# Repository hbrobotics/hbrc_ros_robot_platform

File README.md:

<!--
MIT License

Copyright 2020 Home Brew Robotics Club

Permission is hereby granted, free of charge, to any person obtaining a copy of this
software and associated documentation files (the "Software"), to deal in the Software
without restriction, including without limitation the rights to use, copy, modify,
merge, publish, distribute, sublicense, and/or sell copies of the Software, and to
permit persons to whom the Software is furnished to do so, subject to the following
conditions:

The above copyright notice and this permission notice shall be included in all copies
or substantial portions of the Software.

THE SOFTWARE IS PROVIDED "AS IS", WITHOUT WARRANTY OF ANY KIND, EXPRESS OR IMPLIED,
INCLUDING BUT NOT LIMITED TO THE WARRANTIES OF MERCHANTABILITY, FITNESS FOR A PARTICULAR
PURPOSE AND NONINFRINGEMENT. IN NO EVENT SHALL THE AUTHORS OR COPYRIGHT HOLDERS BE LIABLE
FOR ANY CLAIM, DAMAGES OR OTHER LIABILITY, WHETHER IN AN ACTION OF CONTRACT, TORT OR
OTHERWISE, ARISING FROM, OUT OF OR IN CONNECTION WITH THE SOFTWARE OR THE USE OR OTHER
DEALINGS IN THE SOFTWARE.
-->

# HBRC ROS Robot Platform

The HBRC ROS Robot platform (ie. HR<Sup>2</Sup> or just plain HR2) is a
pedagogical robotic platform for teaching various robotics skills.

This top level document is broken into the following sections below:

* [Google Group](#google-group):
  The Google Group mailing list for this project.

* [Goals/Requirements](#goalsrequirements):
  The goals and requirements for the project.

* [Mechanical](#mechanical):
  The mechanical engineering aspects of the project.

* [Electrical](#electrical):
  The electrical engineering aspects of the project.

* [Software](#software):
  The software engineering aspects of the project.

* [Education](#education):
  The education components of the project.

* [Download, Installation and Workflow](#download-installation-and-workflow):
  The download, installation, and workflow portions of the project.

* [Talks](#talks):
  Various talks given about the project.

## Google Group

There is a Google Groups mailing list to discuss this project at
[HbrcRosRobotPlatform@GoogleGroups.Com](mailto:HbrcRosRobotPlatform@GoogleGroups.Com).
To join the group, visit the
[HBRC ROS Robot Platform web page](https://groups.google.com/d/forum/hbrcrosrobotplatform)
(i.e. `https://groups.google.com/d/forum/hbrcrosrobotplatform`) and request to join.
If that does not work, squirt a quick message to the group manager
(`Wayne` AT_SIGN `Gramlich` PERIOD `Net`) requesting an invitation to join the group.

Not all traffic on the group is going to be interesting to everybody else.
To help out with filtering please put one of the following prefixes at the
front of the each subject line:

* `ALL:` A message of interest to everybody.
* `INST:` A message concerning software installation.
* `ME:` A message to people interested in the HR2 Mechanical Engineering 
  (i.e. solid modeling.)
* `EE:` A message to people interested in the HR2 Electrical Engineering
  (i.e. PCB design, manufacture, bring-up, testing, etc.)
* `SE:` A message to people interested in the HR2 Software Engineering
  (i.e. programs, firmware, etc.)
* `ED:` A message to people interested in the HR2 course materials.
* `DEV:` A message concerning downloading, installation, and development.
* `MSC:` A miscellaneous message that does not really fit any of the above
  protocols.

That should be enough group mailing list structure for starters.

## Goals/Requirements

The list below summarizes the some of the design choices that have been
made so far.

* Start with the Pololu Romi platform used by FPGA class. [Decided]
* Use Patrick's PCB breakout board as a starting point. [Done]
* Consider ditching the Pololu motor board. [Done]
* Work hard to see if the Pololu arm can be bolted on. [Very Likely]
* Try to use USB battery pack instead of AA batteries. [USB Pack yes; AA's no]
* Provide support RasPi 3B+ and RasP4: [yes]
  * 40-pin connector.
  * I2C EEPROM for "hat" identification.
  * Real Time Clock needed for ROS.
  * Various RasPi I2C, SPI, GPO, Serial lines made available.
    *  [Serial: yes, I2C: yes, SPI: probably not, GPIO: OS shutdown
* Some sort of MPU on board:
  * Off the shelf microcontroller board [STM Nucleo-144 Dev. Board format selected]
  * Roomy enough to run MicroPython/MicroROS [STM NUCLEO-F767ZI nominal]
    * ~$25, 216MHz, 2MB Flash, 512K RAM, timers, UARTs, I2C, SPI, Ethernet, etc.
  * Must support C/C++ debugging [ST-Link].
  * Ethernet Phy to talk to boards other than RasPi [Yes]
* FPGA support [custom daughter board required.]
* Arduino support [AVR Dropped. AVR's are expensive/under powered]
* Expansion Capabilities:
  * Arduino Shields. [One can be plugged onto Nucleo.]
  * MikroBus [Iffy, space is tight]
  * Demand Peripherals Connector(s): [On FPGA daughter boards only]
  * Wayne's Bus? [Iffy, space is tight; ouch this hurts!]
  * Grove connectors [Very Likely]
  * Pololu power supply sockets [Iffy, space is tight.]
* Sensors:
  * Motor encoders. [Yes, 1440 step/rev.]
  * Various edge sensors for table top challenge, maze follower, etc.
  * Edge sensors (TOF, IR)
  * Sonars, the are cheap [5 in front, 4 in back.]
  * Servos (arm, camera tilt) [Minimum 4 required]
  * Inexpensive Lidar [Only if the platform is not overloaded]
    * YLidar X2 (~$70)
    * RPLdar A1M8 (~$100)
  * E-Stop [Probably not]
* Camera [RasPi Camera]
* Misc:
  * What issues are missing?

### Mechanical

The mechanical issues are worked out in greater detail in the
[mechancial directory](mechanical/README.md).

The mechanical tasks are:

* Model the Romi platform in OpenSCAD to ensure that the PCB outline
  and mounting holes are correct.
* Model the Romi arm in OpenSCAD to make sure that the Arm does not
  interfere with anything.
* Model both a RasPi 3B+ and RasPi4 for attaching to PCB.
* Model the basic PCB outlines, connector placements, etc.

A short summary of the mechanical design decisions to date are:

* Use the Pololu Romi Platform.
* Use an alternate layout of the motor encoder PCB to free up space to
  support some SBC (Single Board Computers) that are larger than the
  Raspberry Pi footprint.
* Design master board to use an STM Nucleo-144 development board for the
  processor.  All H-bridges, power management, to be put on one board.
* FPGA boards to be done with a a daughter board that plugs into Nucleo-144 board.
 
## Electrical

The electrical issues are worked out in greater detail in the
[electrical directory](electrical/README.md).

Some brief comments on the electrical aspects are:

* The design is to be done using KiCad, since KiCad is 100% free.
* It would be nice to be able to use a simple two layer PCB.
* It would be nice to be able to take power from a USB Power pack.
* It would be nice to support daughter boards for FPGA's.

The overall strategy is to prototype everything using the
[Bantum Labs PCB Milling Machine](https://www.bantamtools.com/)
over at [OLogic](http://www.ologicinc.com/).  This machine is
constrained to only prototyping boards that are 4 inches by 5 inches.
Once the electronics are debugged and working, the PCB's will be
sent out to an appropriate PCB Manufacturing house.

### Software

This section is pretty brief for the moment...

The software issues are worked out in greater detail in the
[software directory](software/README.md).

Terminology:

* Single Board Computer (SBC):
  The nominal SBC for the platform is either the RasPi 3B+
  or the RasPi 4.  Other boards that are compatible with the RasPi
  pin-out *can* be supported, but somebody will have to step up to
  the task of doing the actual support.  The SBC resides on the robot.
* Micro-Processor Unit (MPU):
  This is the micro-controller that is on the main board.
  The nominal processor is ST32Fxxx, where xxx is to be decided.
  The MPU resides on the robot.
* Robot Processors: The robot processors are the SBC and the MPU.
* Development Processor: The development processor is not physically
  attached to the robot.  Instead, it communicates with the robot SBC
  via WiFi.

The software goals are:

* The platform runs ROS on the SBC.
  * Both ROS 1 and ROS 2 are goals with ROS 1 eventually being
    deprecated.
* We need to be able download firmware into the MPU from the SBC.
  This needs to be hands off.
  * Custom C/C++ drivers.
  * MicroPython.
  * Micro ROS.
* The development processor needs to be able to debug code
  running on the robot:
  * Debugging ROS nodes running on the SBC should be relatively easy.
  * Debugging C/C++ code running on the MPU is going to need JTAG
    support.  This can be done with a JTAG chip like the FTDI FT2232.
    This *may* be an "add-on".  OpenOCD can talk to this JTAG chip
    and `gdb` can talk to openocd.
  * Debugging MicroPython is tough.  It currently supports breakpoints
    but does not support data/stack inspection (yet!)
  * As a total stretch, it would be nice to support ARM ETM CoreSight.
    This requires a seriously expensive brick that weighs a ton.
    It is probably a fantasy.
* We need to support FPGA development:
  * We need to be able to download the FPGA chip from the SBC.
  * The FPGA compliation stack needs to run on the SBC and the development
    processor.

## Education

This section is more of a place holder for now...

A partial list of possible educational classes for HR2 platform are:

* Low level robot peripheral drivers.
  * C/C++
  * Micropython
* ROS driver development
  * C/C++
  * Python
* More generic ROS Programming
* Image processing with OpenCV
* AI Frameworks
* Arm manipulation
* PCB design
* MCAD design
  * OpenSCAD
  * Fusion 360
  * FreeCAD
* FPGA class
* Soldering Skills
  * Basic Through Hole
  * Surface Mount
* Rapid PCB prototyping w/Bantum Labs
* etc.

## Download, Installation, and Workflow

Software downloading and installation is done using the following basic steps.

1. [Optional Ubuntu Virtual Machine Installation](#optional-ubuntu-virtual-machine-installation]):
   For now, this project is developed exclusively using a Ubuntu 18.04LTS (Long
   Term Support) Linux distribution.  If you are not running Ubuntu 18.04LTS,
   you need to install it so that it runs using a virtual machine emulation software.
   Otherwise, this step can be skipped.

2. [Download and Install Software](#download-and-install-software):
   The HR2 project uses a diverse set of software.  This software is installed
   using some installation scripts followed by some tried and true technology
   called recursive Make.

3. [Workflow](#workflow):
   Modifications to the documention and design files is done using the
   [GitHub pull request workflow](https://guides.github.com/introduction/flow/).

### Optional Ubuntu Virtual Machine Installation

If you are running on either Windows or MacOS or a non-Ubuntu 18.04LTS Linux distribution,
you need to install Ubuntu 18.04LTS using virtual machine emulation software.  If you are
already running Ubuntu18.04LTS, you can skip this section right now.

There are many
(virtualization)[https://en.wikipedia.org/wiki/Comparison_of_platform_virtualization_software]
software products out there.  If you have a favorite, please feel free to use your favorite
virtualization product.  If you have no favorite, (VirtualBox)[https://www.virtualbox.org/]
is freely available and works.  The remaining instructions are in this section are for
VirtualBox.

Let's start off with some terminology:

* Host Machine:
  The host machine is the actual hardware and associated operating system that VirtualBox
  is running on.

* Guest Machine:
  The guest machine is the virtual hardware and associated operating system that is running
  under the VirtualBox software.  In this case, the guest machine is running Ubuntu18.04LTS.

The basic steps involved are:

1. Download VirtualBox:
   Visit the [VirtualBox Downloads] web page and follow the instructions appropriate
   for your host machine.

2. Download Ubuntu18.04LTS:
   [Download Ubuntu18.04 LTS](https://ubuntu.com/download/desktop) to your host machine.
   This shows up as a file with an `.iso` suffix.
   
3. Configure a VirtualBox Virtual Machine.
   Start VirtualBox software and a Graphical User Interface (GUI) should show up on your
   screen.

   Click on the [New...] button to bring up create pop-up window.

   A. Name and operating system:
      * Name: Pick a name, (suggestion: "Ubuntu18.04LTS").
      * Machine Folder: (Use the default.)
      * Type: Pick [Linux]
      * Version: Ubuntu (64-bit)
      * Click on [Next>].

   B. Memory size:
      * At least 4096 MB is recommended.  Do not use 1024 MB.
      * Click on [Next>]

   C. Hard disk:
      * Select "Create virtual hard disk now".
      * Click on [Create]

   D. Hard disk file type:
      * Select "VDI (VirtualBox Disk Image0"
      *Click on [Next>]

   E. Storage on physical hard disk:
      * Select "Dynamically allocated"
      *Click on [Next>]

   F. File Location:
      * Use the default file folder.
      * Increase the file size to at least 20 GB. 30 GB or 40 GB is preferred.
      * Click on [Create] to create the virtual machine and dismiss the pop-up window.

   G. Configure network:
      * Click on the [Settings...] Button to bring up [Settings] pop-up window:
      * Change "Attached to:" from "NAT" to "Bridged Adapter"
      * Click on [OK] to dismiss the pop-up window.

   The virtual machine is configured and ready to run.

4. Install Ubuntu18.04LTS.

   A. Start the virtual machine by either double clicking on the machine name or clicking
      on the [Start] button.  Please note that the guest machine and host machine can
      fight over who has the keyboard and mouse.  There are two control keys on your
      keyboard, one to the left of the space bar and the other to the right of the space bar.
      The right control key is used break up the fighting over mouse/keyboard input destination.
      If you are going "what happened to my mouse cursor are where are my keystrokes going"
      use the right control key to change things.

   B. After starting the virtual machine, VirtualBox will bring up a pop-up window
      asking you to select a virtual CD Rom image to to insert into the virtual optical
      disk drive.  Please use the file choose to select the Ubuntu 18.04LTS `.iso` file
      you previously downloaded.

   C. Click on [Install Ubuntu].

   D. Select your keyboard.

   E. Select: "Normal installation and download updates".

   F. Select: "Erase disk and install Ubuntu".
      * (Since this is virtual machine you can safely ignore the scary warning.)
      * Select Click on [Install Now]
      * Click on [Continue].

   G. Time Zone:
      *Select the correct time zone.

   H. Account setup:
      * Your name:
        Use your properly capitalize first and last name.
      * Your computer's name:
        Using a lower case name pick a name for the computer.
        For exam
      * Pick a user name:
        All lower case and one word.
      * Choose a password...:
        Type in your password twice.
      * Select "Require my password to log in".

   H. The installation takes some time.

   I. Click on [Restart Now]

   J. Ignore the "Please remove the installation medium" message, just press [Enter].

   K. Just type [Enter] for the Grub splash screen.

   L. Click on you user name and type in your password.

   M. Click through the startup screens.

   N. If the software updater window pops up click on [Install Now] and type in your password.
      If it pops up a restart machine window, just ignore it for now.

5. Install Guest Additions

   The guest extensions provide a more seamless integration between VirtualBox and
   the host machine.  For some reason, the documentation at for VirtualBox guest
   extension installation is actually pretty confusing.  Please try the instructions below:

   A. Bring up a terminal window by typing [Ctrl-Alt-T]  (use the left [Ctrl] key.)

   B. Type the following commands.  `sudo` will probably prompt you for your password.
   
      * `sudo apt update`
      * `sudo apt install build-essential dkms linux-headers-$(uname -r) --yes`

   C. Click on [Devices => Insert Guest Additions CD Image...]

   D. It should ask if it is OK to run some files.  Click [OK].

   E. Type in your password and click [Authenticate].
      This can take a while.

   F. Type [Enter] when [Press Return to close this window...] shows up.
      If your virtual machine reboots you can skip the next step.

   G. (Optional) If for some reason the virtual guest extensions do not properly
      install.  The following commands provide and alternative way of
      getting them installed.  Now run the following commands:

      * `sudo mkdir -p /tmp/cdrom`
      * `sudo mount /dev/cdrom /tmp/cdrom`
      * `sudo sh /tmp/cdrom/VBoxLinuxAdditions.run --nox11`
      * `sudo shutdown -r now`

      The machine should reboot.

   H. Select your user name and login with your password.

   I. Resize the virtual machine window to make sure the guest additions have taken hold.
      The background window should fill as it resizes.  If not, it will stay at a fixed
      size and something has gone wrong with your guest additions install.

   J. In the upper right corner there is a downward pointing triangle.
      Click on it and select [power off].
   
   Your virtual machine is installed and in a powered down state.

6. Make a clone.

   Installing all of the software is sufficiently painful that it is desirable
   to avoid having to do it again.  VirtualBox allows you to make a clone of
   an existing system so that the original system can be reused in the future.
   It is really easy and does not consume very much extra disk space,
   so making a clone is strongly recommended.

   A. Bring up the VirtualBox manager window again.

   B. Right mouse click on the name of your virtual machine:

      * Name: Give the clone a new name like "Ubuntu18.04LTS_HR2"
      * Path: Use the default
      * MAC Address Policy: Use the default
      * Leave the additional options unclicked.
      * Click [Next>] to go to the next pop-up window.

   C. Clone type

      * Select [Linked clone].  This saves lot's of disk space
      * Click on [Clone] to finish the clone.

   D. Now start the clone by by double clicking on it.

## Download and Install Software

The software is generally deployed in three broad catagories:

* Ubuntu packages: for basic tools and software (e.g. Kicad, OpenSCAD, etc.)
* Cloned Git Repositories: this project and some projects it depends upon used
  `git` repositories.
* Python `pip` packages: There is lots of Python 3 code sprinkled around this project
  and a bunch of it is packaged up as Python packages that can be installed with
  the Python `pip` program.  (By the way, `pip` stands for `Pip Installs Packages`.)
  There is heavy use of a technology called Python Virtual Environments.

There will be a number of cloned git repositories and they need to reside as
separate sub-directories under one parent repository directory.  (One parent
directory to rule them all!)  You can call this parent directory whatever you
want -- `repos`, `projects`, `funstuff`, `sauron`, etc.  For the directions
below we use `REPOS` for this parent directory name.  Please substitute the
directory name you picked for `REPOS` in the directions below:

### Clone 

There are 3 broad steps:

1. The first step is to clone the `hbrc_ros_robot_platform` repository.
   Let's get going:

        cd .../REPOS   # Change the current working directory to REPOS
        # We need to get `git` installed.
        # If `git` is already installed, skip the install below:
        sudo apt install git --yes # You may be asked for your user password:
        # Now "clone" the `hbrc_ros_robot_platform` repository using `git`:
	git clone https://github.com/hbrobotics/hbrc_ros_robot_platform.git
        # Change the current working directory to the root of the cloned repository
        cd hbrc_ros_robot_platform
	# Set your `git` user name and `email`.  Please run the following two commands:
        git config --global user.name "Your Name"
        git config --global user.email "youremail@yourdomain.com"

2. The second step is to run one `hr2_install` script.  This is done by

     ./bin/hr2_install OPTION

   where `OPTION` is one or more of the following:
   * `all`:  Installs everything.
   * `most`: Installs everything but `dev`.
   * `dev`:  Installs the development workflow (a personal Git.Hub account is required.)
   * `ee`:   Installs all of the software needed for electrical engineering.
   * `me`:   Installs all of the software needed for mechanical engineering.
   * `sw`:   Installs all of the software needed for software development.

   Many people select the `most` option.

   Downloading everything takes quite a while (frequently in excess of half an hour.)
   Sometime you will be prompted for your user password so that the system can install
   some system software.  The `stm32cubeide` software download (selected by `ee`, `me`)
   is particularly slow.
     
3. After the `hr2_install` script terminates (
   This is important.  You need to activate your Python Virtual environment.
   This is done as follows:

     source ~/.bashrc
     workon hr2   # Activate the hr2 Python virtual environment

4. After that yo can use the `make` program to do any remaining buidling.

   Use the `make` program to recursively build `everything` by typing:

           make everything

Installing is a notoriously fragile process and it is quite possible that
something can go wrong.  If so, please send a message to the group list with
the `DEV:` prefix on the subject line explaining the issue so it can be resolved.

### Workflow

Workflow is a generic term for how modifications are made to this project.

Examples of such modifications are.

* Modifying the mechanical models,
* Modifying electrical design and associated printed circuit board designs,
* Modifying the software,
* Fixing documentation errors,
* Developing educational course materials, Etc.

Some terminology here.  We are going to use the pronoun "you" to mean "you the
person doing project development" in the description below.

#### Workflow Introduction

There are two common workflows supported by GitHub.com:

* Shared Repository Workflow:
  This is the simplest model where there is one common shared parent repository stored
  at GitHub.com and you have local cloned copy of the shared parent repository stored
  locally on your development machine.  You develop and test your changes on your local
  machine.  When you decide your changes are "ready", you "push" the changes back up to
  the shared parent repository on GitHub.com.  Over time, you and other developers
  "pull" the accumulated changes stored in the parent repository down into your
  respective local repositories to stay up to date.  This workflow is extremely
  common and has been supported by many version control systems for literally decades.

* Fork and Pull Request Workflow:
  In this model, the common parent repository is the same as the shared repository
  workflow immediately above.  However, now you need two repositories to do development.
  The first repository is the same local repository on your local machine as before.
  In addition to your local repository, you also have your own semi-private
  repository stored on GitHub.com that is used for staging purposes.  This staging repository
  is goes by a less descriptive name called a "fork repository".  Your fork repository
  is "connected" to the shared parent repository.  Since there are multiple developers,
  there multiple "forks" of the same shared parent directory on GitHub.com, where each
  is stored in a different user account to keep them separate from one another.

  The workflow is that you make modifications to your local repository and "push"
  them up to your staging "fork" repository.  Next, you generate something called
  a "pull request".  (Frankly, the term "pull request" is miss-named, it should be
  called a "merge request".  It is too late to change the terminology now, so we
  will stick with the less descriptive term of "pull request".)  The details of how
  to generate a "pull request" are discussed  little be further below.  The "pull request"
  generates an E-mail that is sent to one or more reviewers.   The reviewer looks at your
  changes using the GitHub.com GUI (Graphical User Interface.)  If the reviewer likes
  the changes, they are immediately accepted and merged from your fork repository to
  the shared master repository.  If any reviewer has some issues, an E-mail dialog ensure
  where the reviewer says things like "I really like this!", "This won't work because ...",
  "Fix this tiny issue", "What about doing it this way...", and an occasional
  "No way because..."  As a result of some of the review comments, you may need to make
  additional changes and push them up to the fork repository.  When the pull-request
  E-mail exchange dialog dies down and all of your changes have been pushed up to your
  fork repository, the reviewer accepts the changes and merges them into the
  shared parent repository.  The "Fork and Pull Request Workflow" is shown immediately
  below using some crude ASCII art:

                [Shared Parent]<---------------[Simi-Private Fork]   GitHub.Com
                       |                                ^
                ====== | ============================== | =====================
                       v                                |
                       +--------->[Private Local]------>+         Local Machine
                        
                         Fork and Pull Request Workflow
			   
The key advantage of the Fork and Pull Request work flow is that you do not need
permission from anybody to start making your changes.  You start your changes locally
and ask for permission only after you think they are ready.  When the reviewer
agrees, your changes are merged in.

It should come as no surprise to you that this project is using the fork and pull
request workflow.

#### Workflow Setup

If you have followed the download and install instructions above, you have a
local copy of the `hbrc_ros_robot_platform` repository as a sub directory under
your REPOS directory.  What you do not have is a staging fork repository *AND*
you have not configured `git` to do an asymmetric pull and push.  The instructions
below will remedy these issues.

Most of the tools you need to do the Fork and Pull Request workflow are already mostly
in place.  The primary tools are `git` and a program called `hub` which is a command
line interface to the GitHub.Com functionality.  We will do as much of the set up using
a command line tools as possible because the command line tools tend not to change as
fast as the web interface changes.  (If you are already comfortable the GitHub.Com web
interface, you can probably skip some of the steps below and use the web interface instead.)

There are a still a few manual steps to do:

1. The first step is to create your own personal account on GitHub.Com.  This is done
   visiting the main [GitHub.Com web page](https://github.com/) web page.  You need to
   specify a unique "Username" (all lower case with no spaces or punctuation is recommended),
   an "Email" address, and a "Password".  There will be a message sent your E-mail address
   that you must respond to with a response E-mail to finish the account creation.  The
   "Username" is your GitHub.Com account name and will be needed further below.  Do not
   log out of GitHub.Com yet.

2. In order to avoid having to type in a password all the time, you need to set up your
   computer to use an SSH key to talk to your GitHub.Com account.  The install scripts
   have ensured that an SSH key has been generated.  The public key is stored at
   `~/.ssh/id_rsa.pub`.  There is a
   [GitHub.Com SSH Key Installation](https://help.github.com/en/github/authenticating-to-github/adding-a-new-ssh-key-to-your-github-account) web page that will guide you through the GitHub.Com
   web interface to install your public SSH key.  It is a little tedium for now, but will avoid
   much password prompting annoyance in the future.  If you are lucky, you should not need
   to deal with the GitHub.Com web interface any more.  Now you can disconnect from GitHub.Com.

3. Add GITHUB_ACCOUNT_NAME variable definition to your `~/.bashrc` file.  This is typically
   done a the end of the file by adding a line that looks like:

      GITHUB_ACCOUNT_NAME=whatever_you_typed_in_in_the_previous_step
      source ~/.bashrc  # Do no forget this step.

4. Please rerun the `hr_install dev` to get your development environment set uo.

That pretty much wraps up the additional steps need to enable the "Fork and pull-request"
workflow.  Next, it is time to try it out.

#### Workflow Usage

The `git` program does a great deal of stuff and it is outside the scope of this
document to attempt to cover it all.  Instead, we will explain just enough to get started.

If you have followed the steps above, you have a repository named `hbrc_ros_robot_platform`
sitting on you local machine.  Your local repository has the following characteristicx:

* It has `upstream` remote descriptor that points to the shared project repository.
* It has `staging` remote descriptor that points to the semi-private forked directory
  that is used for staging purposes.
* The `master` branch which has be set up so that it only accepts updates from the
  `upstream` remote.

The first thing to understand is that you should never to development on the `master`
branch.  We have tried to make it difficult for you to screw up `master`, but somebody
who really wants to can screw it up anyhow.

The second thing to understand is that all development takes place in one or more
side branches, called development branches.  The way to create a new branch is by

     git checkout -b NEW_BRANCH_NAME master

where you supply a new and hopefully descriptive name for the new development branch.
After this command, the new branch will be active.  Now you can modify things to your
hearts content.  You can check the files in as many times as you want using `git add ...`
and `git commit -m "SOME MESSAGE HERE."`.  You can perform as many commits as you want
on the branch.  Please put descriptive comments in the commit logs.

When you think you changes are ready to be merged into the project you initiate
a pull-request.  This is done by the command:

     pull_request

This command is in the repository `bin` directory.  This will ensure that you have
merged with the `master` branch, push your commit up to the staging repository and
generate a pull request.  You will have add a comment into the pull request via an
editor that will pop up.

Just so you know, there is a command called `master_merge` that will ensure that
the `master` branch is up to date with GitHub.Com and then attempt to `master` branch
to be merged with your current branch.  This command is invoked by `pull_request`, but
you can invoke it yourself if you just want to merge without triggering a pull request.

That is basically it.

The current files in the `bin` directory are:

* `hr2_install`:
  An installation script for install HR2 project software.

* `master_merge`:
  A script that ensures that the `master` branch is up to date and then attempts
  to merge the `master` branch into your branch.

* `pull_request`:
  A script the forces a `master_merge` followed by generating a pull request for GitHub.Com.

* `stm32cubeide`:
  A symbolic link to a `stm32cubeide` program.  This is basically the Eclipse programming
  environment that has been configured to work with the `stm32cube` software for supporting
  STM32 micro-controllers.

* `xstm32cubeid`:
  This is a shell script that attempt to attach to an externel (i.e. remote) ST-Link
  before starting the stm32cube.
  This is preformed using an the `usbip` (i.e. USB Internet Protocol) for remote access to USB devices.

More scripts are likely to be added over time.

#### Coding Style

The vast majority of the code is written in Python, C, and some Shell scripts.

* Python:
  Python 3 only.  All of the code is pushed through `mypy` (with type-hinting),
  `flake8` to catch coding issues, and `pydocstyle` to catch documentation issues.
  In general, the pretty standard coding style for Python is used.  One quirk is that
  Wayne Gramlich hates the `self` variable and usually assigns it to a more descriptive
  variable name.  Other than that, it is pretty standard.

* C:
  Pretty standard C coding style is used.  There are 4 spaces for each indentation level.
  The "then" clause of an if statement always has {...}, no exceptions.

* Shell:
  Shell scripts are tedious to write and debug and still tend to be fragile.
  Lot's of comments are used.  The `set -xeuo pipeline` command is used for debugging
  when possible.

All documentation is written in [markdown](https://daringfireball.net/projects/markdown/).
Speaking of documentation, it is treated just like code in that it has bugs in it as well
(miss-spelled words, bad grammar, unclear desciptions, etc.)  The documentation is fixed
the same way that code is fixed, using the standard workflow.

Eventually we will use the Github issue tracker to track both code and documentation issues.
For now, the group mailing list will be used instead.

## Talks

Occasionally, talks are give about this project and the talk materials are organized into the 
[talks](talks/README.md) directory.

<!-- Random

        ;;; Make emacs notice when buffers change due to switching branches:
        (global-auto-revert-mode 1)

#### Stm32CubeIDE

* Downloand `en.st-stm32cubeide_1.3.0_5720_20200220_1053_amd64.deb_bundle.sh.zip`from STM website.
* `mkdir /tmp/cube`
* `unzip -d /tmp/cube en.st-stm32cubeide_1.3.0_5720_20200220_1053_amd64.deb_bundle.sh.zip`
* Unpacks into `st-stm32cubeide_1.3.0_5720_20200220_1053_amd64.deb_bundle.sh`
* Set execute bit `chmod +x st-stm32cubeide_1.3.0_5720_20200220_1053_amd64.deb_bundle.sh`
* Execute `/tmp/cube/st-stm32cubeide_1.3.0_5720_20200220_1053_amd64.deb_bundle.sh`
  * It prompts for sudo password.  Not clear what it does under sudo.
* Unpacks a bunch of stuff into the `/opt/st/stme2cubeide_1.3.0_stm32` directory.
* Execute `/opt/st/stm32cubeide_1.3.0_stm32/stm32cube`

#### Removing big binary blobs:

We are trying to delete: `stm32cube_download/stm32cube.tar.bz2.0{0,1,2,3,4,5,6,7,8}` from
the repository.  It looks like `bfg` is the recommended program for doing the deletion.
Make sure that the files have been `git delete`'ed and pushd up to GitHub.Com.
Rename the current repo from `kicube32` to `kicbube32_delete_me`.  Hopefully we will
not be using the repo any longer...

Some URL'S:

* [BFG](https://rtyley.github.io/bfg-repo-cleaner/)
* [BFG Example](https://github.com/IBM/BluePic/wiki/Using-BFG-Repo-Cleaner-tool-to-remove-sensitive-files-from-your-git-repo)
* [Another BFG Example](https://medium.com/@prankulgarg/want-to-remove-large-files-blobs-from-git-history-permanently-4723e72a84e1)

     # Download the repository to be modified:
     cd /tmp
     time git clone --mirror git@github.com:waynegramlich/kicube32.git
     # Generates a file called `/tmp/kicube32.git`.

     # Make a backup:
     time tar xvf /tmp/kicube32.git.tar kicube32.git.tar

     # Download `bfg`:
     # `wget https://repo1.maven.org/maven2/com/madgag/bfg/1.13.0/bfg-1.13.0.jar -O /tmp/bfg.jar`

     # Make sure we have java installed:
     which java

     # Run `bfg`:
     time java -jar bfg.jar --delete-files stm32cube.tar.bz2.0{0,1,2,3,4,5,6,7,8} /tmp/kicube32.git

     # Do final cleaunp:
     cd /tmp/kicube32.git
     time git reflog expire --expire=now --all && git gc --prune=now --aggressive

     # See how you did:
     du -sh *

     # Add a remeote back in:
     git remote add upstream git@github.com:waynegramlich/kicube32.git
     git push --force upstream master

    * https://stackoverflow.com/questions/6335717/can-git-tell-me-if-a-merge-will-conflict-without-actually-merging

        git merge --no-commit branch2
        # check the return code here
        git merge --abort

;;; Make emacs notice when buffers change due to switching branches:
(global-auto-revert-mode 1)

-->

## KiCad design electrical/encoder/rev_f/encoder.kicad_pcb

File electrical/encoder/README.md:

# HR2 Encoder

The HR2 Encoder deals with the geometry constraints of a the Robot Computer
(i.e. Raspberry Pi 4) mounted on the Pololu Romi Base.
There is only one way to mount the Raspberry Pi processor on the Romi.
This means that the standard Pololu Romi encoders will not work.
Thus new encoders are needed.
These encoder boards are soldered to the motor and have 2 male 1x3 right angle connectors
that plug into 2 associated female 1x3 receptacles on the master board.
The connectors are to the side of each motor.

The Pololu encoder schematic uses the Diodes Incorporated AH1751 in the SOT23 package.
The AH1751 has A Bhys (Magnetic field hysteresis) 75 Gauss = 7.5mT
The CGS units for magnetic field strengths are Gauss and the MKS units are Tesla.
To convert from Gauss to Tesla, divide by 10000 (note: 10^4, not 10^3!)

The recommended replacement is the DI AH1751 is the DI AH3774.
Instead, for Rev. C and Rev D. the TI DRV5013 is used.
The AH1751 has A Bhy (Magnetic field hysteresis) 75 Gauss = 7.5mT
The TI DRV5013 has 4 versions of the chip that have different Bhys:
* FA: 2.6mT
* AD: 5.4mT
* AG: 12mT
* BC: 24mT
The closest match to the DI AH1751 is the TI DRV5013AD.

There are the following versions:

1. [Rev A.](#rev_a):
   The Rev A. boards had the 2 F1x3 offset by .1inch and had to refabricated.

2. [Rev B.](#rev_b):
   The Rev B. boards were designed using an incorrect hall effect sensor.
   A unipolar rather than a bipolar sensor was selected.
   In addition there was insufficient clearance for the motor hub to fit through the encoder PCB.

3. [Rev C.](#rev_c):
   The Rev C. boards are correct, but the right encoder mating connectors on the Rev. A
   master board are wired up backwards.

4. [Rev D.](#rev_d):
   The Rev D. board is an encoder board that works around the inverted wiring
   on the Rev. A master board, by inverting the wiring on the encoder.
   Thus, this board is only meant to be used as the Right encoder for the Rev. A  master board.

5. [Rev E.](#rev_e):
   A board spin on Rev.C that swaps a ground pin with quadrature signal to match a corresponding
   error on Master Board Rev. A.
   The hub hole is the wrong size.  (How did that happen?)

6. [Rev F.](#rev_f):
   A board spin on Rev.D that swaps a ground pin with quadrature signal to match a corresponding
   error on Master Board Rev. A.
   The hub hole is the wrong size.  (How did that happen?)

<!--
Pin locations are from left to right facing the top side are:
Left Side:
* 1: GND
* 2: QUADA
* 3: QUADB

Right Side:
* 4: VCC (3.3V-5V)
* 5: MOTOR-
* 6: MOTOR+

Motor tabs:
* 7: MOTOR- (Left tab)
* 8: MOTOR+ (Right tab)

LQUAD_A:
* PD12: CN10-21  LPTIM1_IN1 (CN12-43)

LQUAD_B: (Two pins shorted together)
* PA4: CN7-17  (CN11-32)
* PE1: CN10-24 LPTIM1_IN2 (CN11=61)

RQUAD_A:
* PC6: CN7-1 TIM8_CH1 (CN12-04)

RQUAD_B: 
* PC7: CN7-11 TIM8_CH2 (CN12-19)

GND:
* CN8-13
* CN9-23
* CN9-12
* CN7-8
* CN10-5
* CN10-17
* CN10-27
* CN10-22

+3.3V:
* CN8-7

+5V:
* CN8-9

Rev E: Left to right from front side:  Works for left motor.
1: QUADB
2: QUADA
3: GND
4: VCC
5: MOTOR+
6: MOTOR-

Rev F: Left to right from front side:   Works for right motor.
6: MOTOR-
5: MOTOR+
4: VCC
3: GND
2: QUADA
1: QUADB

-->

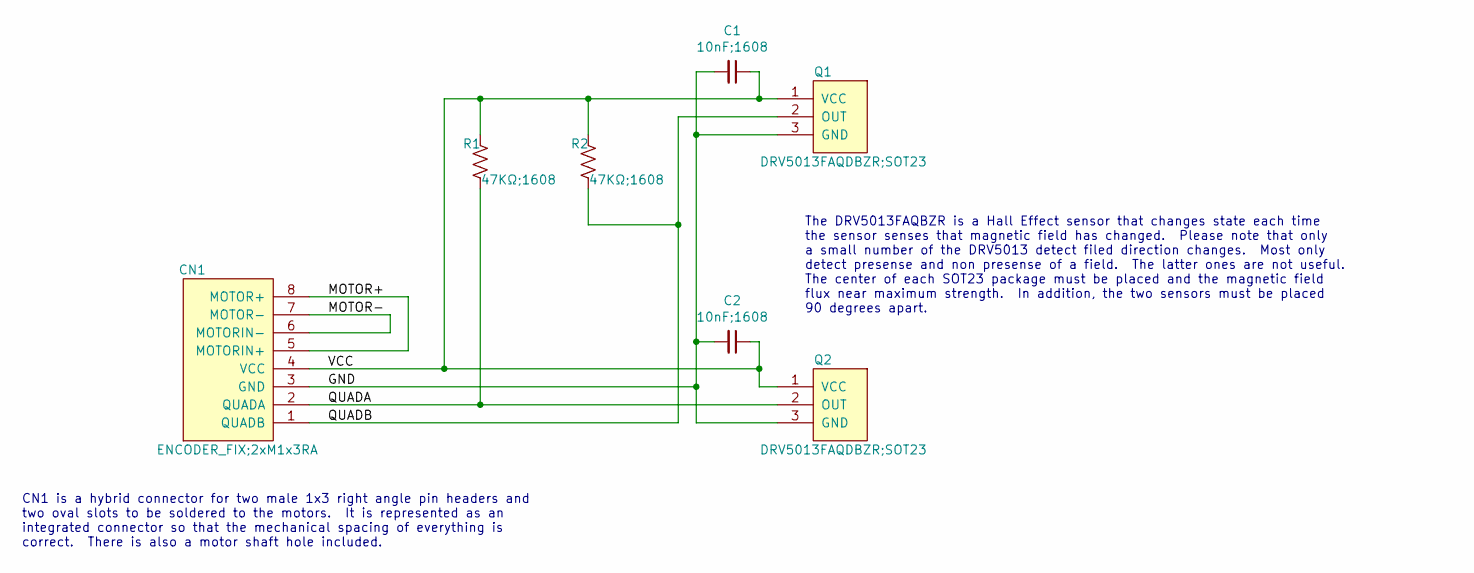
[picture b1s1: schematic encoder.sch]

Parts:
C1, C2: 10nF;1608; C_0603_1608Metric
CN1: ENCODER_FIX;2xM1x3RA; ENCODER_2xM1x3RA
Q1, Q2: DRV5013FAQDBZR;SOT23; SOT-23
R1, R2: 47KΩ;1608; R_0603_1608Metric

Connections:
/GND: C1.2, C2.2, CN1.3 (GND), Q1.3 (GND), Q2.3 (GND)
/MOTOR+: CN1.5 (MOTORIN+), CN1.8 (MOTOR+)
/MOTOR-: CN1.6 (MOTORIN-), CN1.7 (MOTOR-)
/QUADA: CN1.2 (QUADA), Q2.2 (OUT), R1.2
/QUADB: CN1.1 (QUADB), Q1.2 (OUT), R2.2
/VCC: C1.1, C2.1, CN1.4 (VCC), Q1.1 (VCC), Q2.1 (VCC), R1.1, R2.1

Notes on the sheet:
The DRV5013FAQBZR is a Hall Effect sensor that changes state each time the sensor senses that magnetic field has changed. Please note that only a small number of the DRV5013 detect filed direction changes. Most only detect presense and non presense of a field. The latter ones are not useful. The ce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
CN1 is a hybrid connector for two male 1x3 right angle pin headers and two oval slots to be soldered to the motors. It is represented as an integrated connector so that the mechanical spacing of everything is correct. There is also a motor shaft hole included.

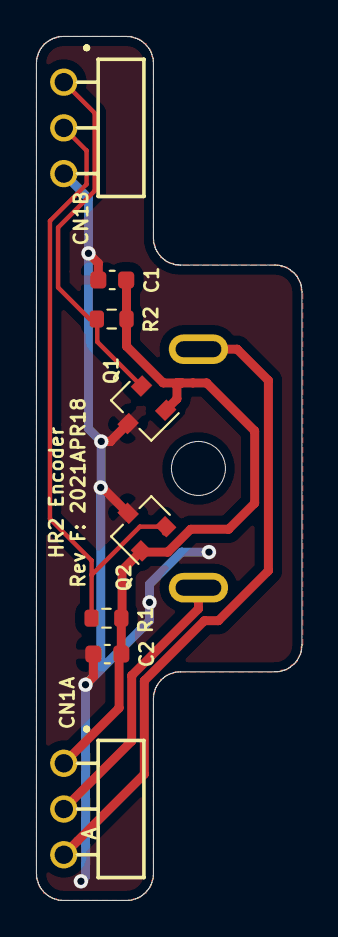
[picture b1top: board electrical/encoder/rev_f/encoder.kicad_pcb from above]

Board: 2 copper layers, 14.8 x 48.0 mm, 7 parts (1 on the bottom side), 6 nets.

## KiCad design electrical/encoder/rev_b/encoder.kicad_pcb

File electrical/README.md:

<!--
MIT License

Copyright 2020 Home Brew Robotics Club

Permission is hereby granted, free of charge, to any person obtaining a copy of this
software and associated documentation files (the "Software"), to deal in the Software
without restriction, including without limitation the rights to use, copy, modify,
merge, publish, distribute, sublicense, and/or sell copies of the Software, and to
permit persons to whom the Software is furnished to do so, subject to the following
conditions:

The above copyright notice and this permission notice shall be included in all copies
or substantial portions of the Software.

THE SOFTWARE IS PROVIDED "AS IS", WITHOUT WARRANTY OF ANY KIND, EXPRESS OR IMPLIED,
INCLUDING BUT NOT LIMITED TO THE WARRANTIES OF MERCHANTABILITY, FITNESS FOR A PARTICULAR
PURPOSE AND NONINFRINGEMENT. IN NO EVENT SHALL THE AUTHORS OR COPYRIGHT HOLDERS BE LIABLE
FOR ANY CLAIM, DAMAGES OR OTHER LIABILITY, WHETHER IN AN ACTION OF CONTRACT, TORT OR
OTHERWISE, ARISING FROM, OUT OF OR IN CONNECTION WITH THE SOFTWARE OR THE USE OR OTHER
DEALINGS IN THE SOFTWARE.
-->
<!-- <<<<<<<<<<<<<<<<<<<<<<<<<<<<<<<<<<<<< 100 characters >>>>>>>>>>>>>>>>>>>>>>>>>>>>>>>>>>>>>> -->

# HR2 Electrical Directory

The overall architecture of the `electrical/` directory is:

* `README.md`:
  A this document written in markdown format.
* `docs/`:
  A sub-directory containing documentation.
* `orders/`:
  A sub-directory contain per order information.
  This includes schematic symbols, PCB footprints, and parts ordering information.
* `master_board/`:
  The design files for the main HR2 master PCB.
  The master board also has the `STM32CubeIDE` project file for pin assignment
  and associated firmware generation to configure the microcontroller.
* `st_adapter/`:
  The design files for the ST-Link adapter PCB.
* `encoder/`:
  The design files for shaft encoder PCB.
Over time, additional PCB's a will be added.

Each PCB directory is broken into revision sub-directories:

  * `rev_a/`:
    This is the first PCB revision.
  * `rev_b/`
    This is the second PCB revision
    (only started after the first version has been built.)
  * etc.

The `orders` sub-directory is broken into a sequence of sub-directories labeled
`order1/`, `order2/`, `order3/`, ...
The `order`*N* sub-directory attempts to capture all of the schematics symbols,
PCB footprints, and electrical/mechanical parts that are all ordered together
(e.g. PCB Gerbers go to PCB fabrication and parts lists go to parts vendors.)
The requirement is that all PCB's share a consistent set of PCB footprints,
schematic symbols, and electrical parts.

After the orders go out.  All of the existing PCB's and contents of the
associated files are locked down into a `git` repository.  This is so that
subsequent revisions do not the existing designs.  For the next revisions,
a new `order`*N+1* sub-directory is created.  Many of the symbols from the
previous `order`*N* sub-directory into the `order`*N+1* sub-directory,
where they can be freely modified to without breaking any of the older revisions.

The contents of an `order`*N*`/` directory are:

* `Makefile`:
  This is used by the `make` program to build everything.
* `pretty/` sub-directory:
  This is a sub-directory where all of the shared KiCad PCB footprints live.
* `kiparts/` sub_directory:
  This is a sub-directory of `.csv` files,
  that specify the various rectangular schematic symbols definitions are stored.
  There is a program called [`kipart`](https://kipart.readthedocs.io/en/latest/)
  that takes a `.csv` file and generates a bot the `.lib` and `.dcm` file.
  Since many schematics are full of square modules, program generates the square
  schematic symbols with the right pin names, numbers, and signal types,
  it is generally easier to use `kipart` to manage KiCad schematic symbols than
  to use the KiCad schematic symbol library.
* `order`*N*`.lib`:
  This is the library of generated schematic symbols.
* `order`*N*`.dcm`:
  This is the schematics symbol documentation file.
  
The design rules for schematic capture are:

* Almost all text is horizontal.
  The only  exceptions only allowed for "stock" schematic symbola) that come with KiCad.
* Most rectangular symbols have wires coming out vertically connections are horizontal.
  There can be an occasional exception.
* All net names are upper case letters and digits.  An lower case `n` can be used
  as a prefix indicate an active low logic line.
* All wires are on a rectangular grid.
* When possible try to organize the schematic such that inputs are on the left
  and outputs are on the right.
* Hierarchical design is used to organize the sheets.
* Try to keep "air wires" to a minimum.
  Instead use "blue" buses to help reduce the wire mazes.
* Make all power and ground connections explicit.
* Footprint names are metric (e.g. 1608 instead of 0603.)
* Footprint names are of the form *part_name*`;`*footprint_name*.
* Resistors use the older American "3 hump" style of resistor.
* Resistance values use the ISO unit symbol of Ω.
* Capacitance values use the units of µF, nF, and pF.

<!--

[Raspian Shutdown Button](https://www.quartoknows.com/page/raspberry-pi-shutdown-button#:~:text=Press%20the%20shutdown%20button.,stopped%2C%20aborting%20the%20shutdown%20procedure.)

USB2 Micro connector Pinouts:

USB_Micro-B_Amphenol_10103594-0001LF_Horizontal

  USB_MICRO_B;S+T:FCI_10118194_0001LF;CONN USB MICRO B RECPT SMT R/A 1:[bus_loki: N23]
    Newark element14:67T2260 [Amphenol: 10118194-0001LF] 1/$0.403 10/$0.388 

1: VBUS +
2: D-
3: D+
4: ID
5: GND

H-Bridges

MTS62C19A: Pretty complicated, current sense resistor.  $1.09
TC78H651xxx: 7V max $1.25
LV8549MC: 1 Amp total output. $1.29

TI: DRV8870DDAR dumb dual H-bridge, NFET's; no thermal; $1.92

Grove:

All:
  pin3=VCC
  pin4=GND
Digital:
  pin1=Dn (bi_directional)
  pin2=Dn+2 (bi_directional)
Analog:
  pin1=An (Analog)
  pin2=Dn+2 (Analog)
UART:
  pin1=RX
  pin2=TX
I2C:
  pin1=SCL
  pin2=SDA

Part Number	Pin 1	Pin 2	Size	Part		Title
101020000	RX	TX	N/S			Serial	Grove - Serial Camera Kit  Serial
101020001	A0	NC	1x1	WSP2110		HCHO Sensor
101020002	A0	NC	1x2			GROVE GAS SENSOR(O2)
101020003	D0	NC	1x1			GROVE BUTTON (pull down resistor)
101020004	D0	NC	1x1			GROVE SWITCH
101020005	D0	NC	1x1	MVS0608.02	Collision
101020006	A0	NC	1x2	MQ-3		Gas Sensor (alchool)
101020008	A0	NC	1x3~			Moisture Sensor
101020009						Line Finder (obsolete)
101020010	A0	NC	1~x2~			Ultrasonic Ranger
101020011	A0	NC	1x2	DHT11		Temp/Humidity Sensor
101020012	A0	NC	--			Dust Sensor
101020013	SCL	SDA	--	DS1307		Real Time Clock
101020014				GL5528, LM358	Grove Light Sensor (Digi-Key discontinued)
101020015	A0	NC	1x1	LM358, NCP18WF104	Temperature Sensor
101020016	NC	SIG	1x1	TSOP382		Infrared Receiver
101020017	A0	NC	1x1			Rotory Angle Sensor (potentiometer)
101020018	A0	NC	1x1			Water Sensor
101020019	A0	NC	1x2	AM2302		Humidity Sensor
101020020	D0	NC	1x2			PIR Motion Sensor
101020021						Air Quality Sensor  (obsolete)
101020022						Light Sensor  (obsolete)
101020023	A0	NC	1x1	LM386		Sound Sensor
-
101020025	D0	NC	1x1	LM386		Tilt Switch

101020017	A0	NC	1x1			Rotary Angle Sensor (10K Pot)
101020025	Dn	NC	1x1			Tilt Switch (digital)
101020028	A0	A1	1x2			Thumb Joystick (2 20K Pot's)

There are plenty of timers left.

Lidar Notes:

Lidars are kind of a mess.  All of them have different interfaces.  The right strategy
is a daughter board strategy.  The maximum number of pins seems to be 7:
  * VCC (5V)
  * GND (0V)
  * TX (3.3V)
  * RX (3.3V)
  * MOTOR_PWM (3.3v)
  * MOTOR_EN (3.3v)
  * DEV_EN (3.3V)
This board can be quite small.

* YDLIDAR X2:
  * Cost: $69US
  * Range: 8m
  * Voltage 4.8V - 5V - 5.2
  * Start current: 300mA - 400mA - 500 mA
  * Working current: 200mA - 350mA - 380 mA
  * RPM: 5Hz - 8Hz
  * Pins:
    * M_CTR (PWM or volatage) 0V - 1.8V 3.3V. 0% duty cylce => full speed .
    * GND
    * Tx  (115200 8N1) 1.8V -3.3V - 3.5V
    * VCC

* YDLIDAR X4:
  * Cost: $99US
  * Range 10m
  * Scan Rate: 6-12Hz
  * Volatage: 4.8V - 5V - 5.2V
  * Start Current: 400mA - 450mA - 480mA
  * Working Current: 330mA - 350mA - 380mA
  * Pins:  PH1.25-8P
    * VCC 5V
    * Tx 3.3V 128000 8N1
    * Rx 3.3V
    * GND
    * M_EN (Motor Enable) 3.3V
    * DEV_EN (Device Enable) 3.3V
    * M_SCTP (Motor Speed Control) Voltage or PWM 0-3.3
    * NC
  
* RPLidar A1M8:
  * Cost: $99US
  * 115200 8N1
  * Voltage: 5V(typical) - 9V
  * MOTOCTL: 0V - VMOTO
  * VCC_5: 5V
  * TX: 0-5V
  * RX 0-5V
  * Start Current 500mA - 600mA
  * Working current: 300mA - 350mA
  * Pins
    * Connector 1:  PH1.25-4P
      * TX 115200 8N1 3.3V
      * RX
      * VCC
      * GND
    * Connector2:  PH1.25-3P
      * VMOTOR 5V (9V max)
      * MOTOCTL
      * GND

* YDLIDAR G2:
  * Cost: $159US
  * Range: 12m
  * Scan Rate: 5-12Hz
  * Voltage 4.8-5.0-5.2V
  * Start Current: 550mA-600ma-650mA
  * Sleep: <50mA
  * Working Current: 250mA-300mA-350mA
  * Pins: PH1.125-5P
    * NC
    * GND
    * Rx (230400 8N1) 3.3V
    * Tx
    * VCC

* YDLIDAR G4:
  * Cost $304.20US
  * Range: 16m
  * Scan Rate: 5-7-10Hz
  * Voltage: 4.8-5-5.2V
  * Start Current: 700-800-850mA
  * Standby Current: < 50mA
  * Working Current: 350-400-450mA
  * Pins same as G2

SPI Devices:

The STM32F676 has 6 SPI interfaces and support NSS and TI mode.
* SPI1, SPI4, SPI5, and SPI6 can operate at 54MBits/sec.
* SPI2 and SPI3 can operate at 25Mbits/sec.
The STM32F676 has 3 S2C interfaces:
* SPI1, SPI2, SPI3.

-->

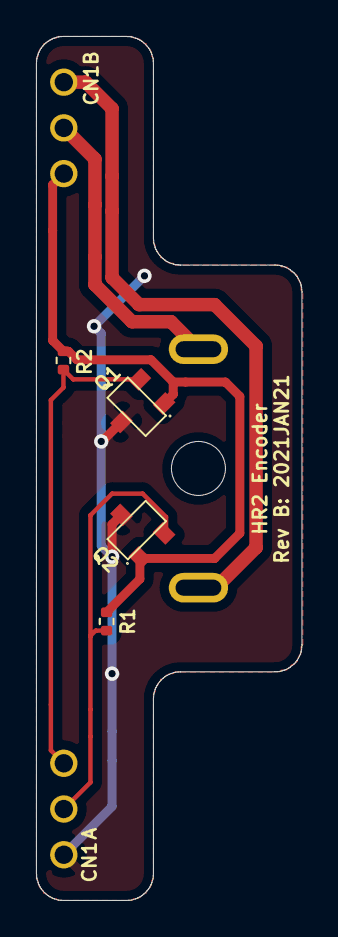
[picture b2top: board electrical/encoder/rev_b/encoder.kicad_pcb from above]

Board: 2 copper layers, 14.8 x 48.0 mm, 5 parts (0 on the bottom side), 6 nets.

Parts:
CN1: ENCODER;2xM1x3RA; ENCODER_2xM1x3RA
Q1, Q2: AH1806;SC59; SC59
R1, R2: 100Ω;1005; R_0402_1005Metric

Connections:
/GND: CN1.1, Q1.2, Q2.2
/MOTOR+: CN1.5, CN1.8
/MOTOR-: CN1.6, CN1.7
/QUADA: CN1.2, Q2.3, R1.2
/QUADB: CN1.3, Q1.3, R2.2
/VCC: CN1.4, Q1.1, Q2.1, R1.1, R2.1

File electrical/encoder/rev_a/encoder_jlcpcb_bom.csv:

"Comment","Designator","Footprint","LCSC Part #","Mfg Part No."
"AH1806;SC59","Q1, Q2, ","SOT-23-3","C126664","AH180N-WG-7"
"100KOhm;1005","R1, R2, ","0402","C25741","0402WGF1003TCE"

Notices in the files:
electrical/encoder/rev_a/encoder.sch:
License: MIT
electrical/master_board/rev_a/master_board.kicad_pcb:
Copyright © 2019-2020:
HomeBrew Robotic Club
